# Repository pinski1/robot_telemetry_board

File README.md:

# Robot Telemetry Board

[Telemetry firmware available here](https://github.com/mjg59/robot_telemetry_viewer)

board files in ./board

schematic in ./output

See the "bridge" directory for code to use this board as an opto-isolated
USB serial bridge.

See the "analysis" directory for code used to analyze the resulting logs.

You can [buy the PCB directly from
OSHPark](https://oshpark.com/shared_projects/APZSUiwL) if you'd like to use it.

If you use the board, it would be super cool of you to give us credit.

The BOM is in BOM.csv

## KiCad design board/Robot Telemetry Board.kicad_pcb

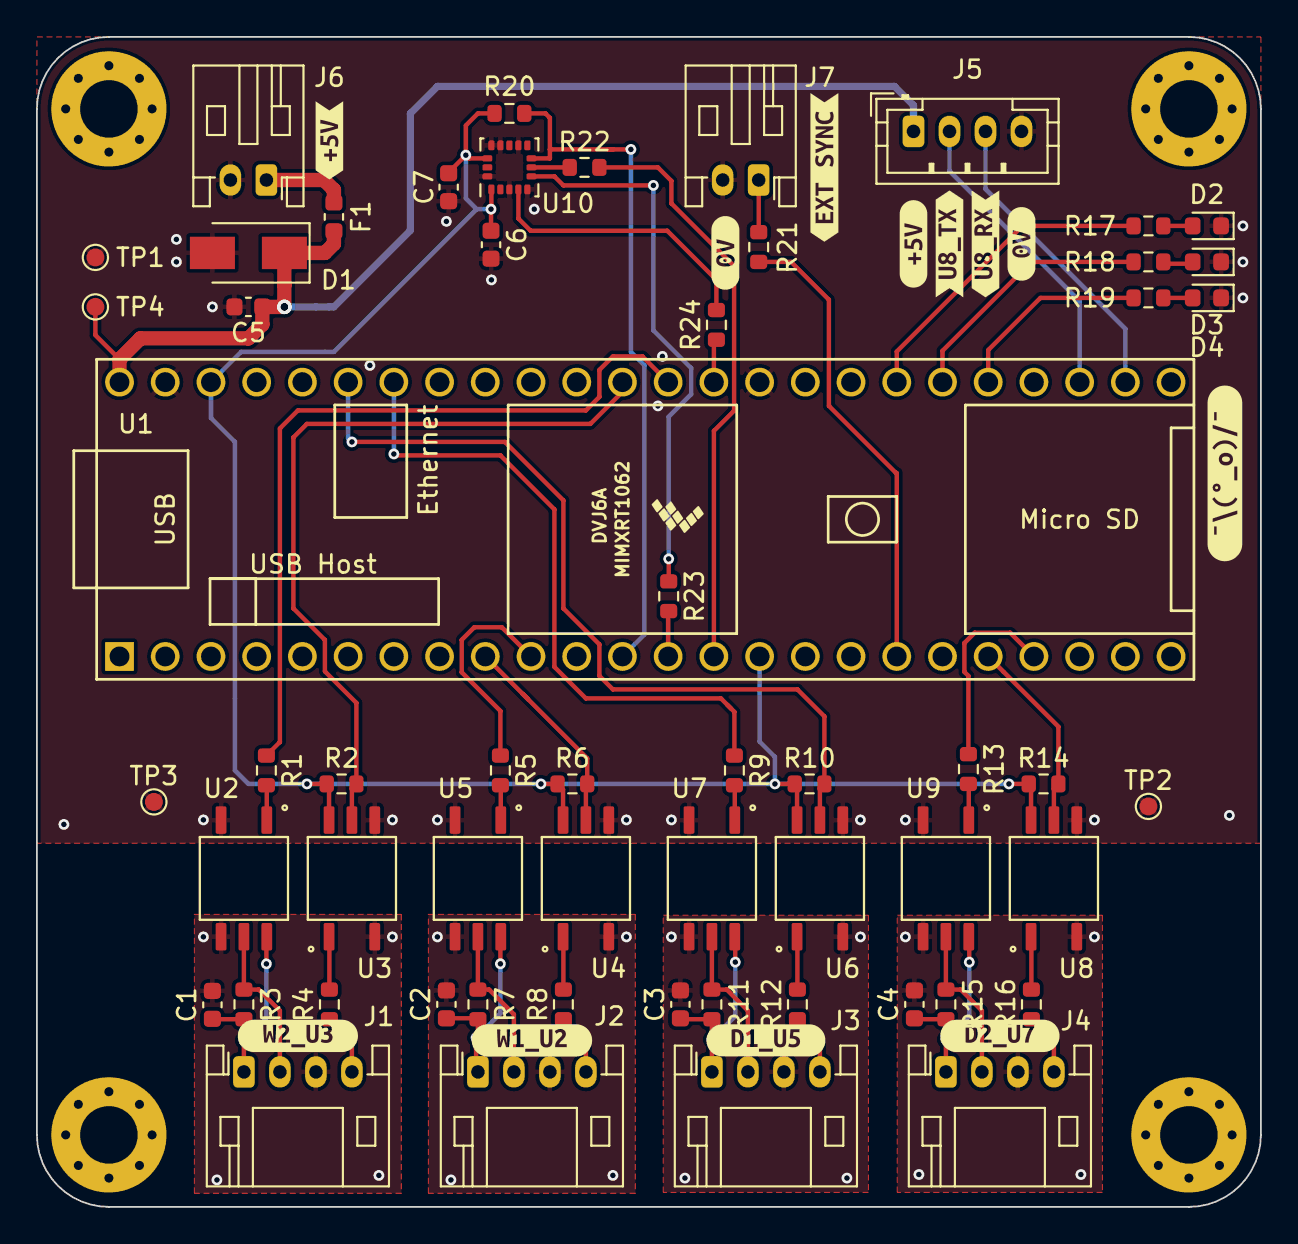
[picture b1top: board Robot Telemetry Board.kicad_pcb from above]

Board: 2 copper layers, 68.0 x 65.0 mm, 73 parts (0 on the bottom side), 53 nets.

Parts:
C1, C2, C3, C4, C6, C7: 100nF; C_0603_1608Metric
C5: 1uF; C_0603_1608Metric
D1: SMAJ5.0AQ-13-F; D_SMA
D2, D3, D4: LED; LED_0603_1608Metric
F1: 200mA; Fuse_0603_1608Metric
H1, H2, H3, H4: MountingHole; MountingHole_3.2mm_M3_Pad_Via
J1, J2, J3, J4: Conn_01x04; JST_PH_S4B-PH-K_1x04_P2.00mm_Horizontal
J5: Conn_01x04; JST_PH_B4B-PH-K_1x04_P2.00mm_Vertical
J6, J7: Conn_01x02; JST_PH_S2B-PH-K_1x02_P2.00mm_Horizontal
R1, R2, R3, R4, R5, R6, R7, R8, R9, R10, R11, R12, R13, R14, R15, R16, R17, R18, R19: 1k; R_0603_1608Metric
R20: 10k; R_0603_1608Metric
R21, R22, R23, R24: 100R; R_0603_1608Metric
TP1, TP2, TP3, TP4: TestPoint; TestPoint_Pad_D1.0mm
U1: Teensy4.1; Teensy41_DIP
U2, U3, U4, U5, U6, U7, U8, U9: VOM452T; SOIC127P700X230-5N
U10: ADXL372; LGA-16_3x3mm_P0.5mm_LayoutBorder3x5y
kibuzzard-61D772F0: G***; kibuzzard-61D772F0
kibuzzard-61D773E1: G***; kibuzzard-61D773E1
kibuzzard-61D773F7: G***; kibuzzard-61D773F7
kibuzzard-61D7731E: G***; kibuzzard-61D7731E
kibuzzard-61D7737B, kibuzzard-61D7737B#2: G***; kibuzzard-61D7737B
kibuzzard-61D7742A: G***; kibuzzard-61D7742A
kibuzzard-61D7757F: G***; kibuzzard-61D7757F
kibuzzard-61D77360: G***; kibuzzard-61D77360
kibuzzard-61D77558: G***; kibuzzard-61D77558
kibuzzard-61D77572: G***; kibuzzard-61D77572
kibuzzard-61D77595: G***; kibuzzard-61D77595

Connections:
+3V3: C6.1, C7.1, R2.1, R6.1, R10.1, R14.1, R20.2, U1.15 (3V3), U1.46 (3V3), U3.6, U4.6, U6.6, U8.6, U10.1 (VDDIO), U10.14 (VS)
+5V: C5.1, D1.1 (A1), F1.1, J5.1, TP4.1, U1.48 (VIN)
/D_VESC1_UART5_RX: R10.2, U1.43 (21_A7_RX5_BCLK1), U6.5
/D_VESC1_UART5_TX: R9.1, U1.42 (20_A6_TX5_LRCLK1)
/D_VESC2_UART7_RX: R14.2, U1.20 (28_RX7), U8.5
/D_VESC2_UART7_TX: R13.1, U1.21 (29_TX7)
/EXT_SYNC: R21.2, U1.18 (26_A12_MOSI1)
/ISO_UART1/ISO_RX: J1.4, R4.1
/ISO_UART1/ISO_TX: J1.2, R3.2, U2.5
/ISO_UART1/VDD: C1.1, J1.1, R3.1, U2.6
/ISO_UART1/VSS: C1.2, J1.3, U2.4, U3.3
/ISO_UART2/ISO_RX: J2.4, R8.1
/ISO_UART2/ISO_TX: J2.2, R7.2, U5.5
/ISO_UART2/VDD: C2.1, J2.1, R7.1, U5.6
/ISO_UART2/VSS: C2.2, J2.3, U4.3, U5.4
/ISO_UART3/ISO_RX: J3.4, R12.1
/ISO_UART3/ISO_TX: J3.2, R11.2, U7.5
/ISO_UART3/VDD: C3.1, J3.1, R11.1, U7.6
/ISO_UART3/VSS: C3.2, J3.3, U6.3, U7.4
/ISO_UART4/ISO_RX: J4.4, R16.1
/ISO_UART4/ISO_TX: J4.2, R15.2, U9.5
/ISO_UART4/VDD: C4.1, J4.1, R15.1, U9.6
/ISO_UART4/VSS: C4.2, J4.3, U8.3, U9.4
/LED1: R17.1, U1.31 (39_MISO1_OUT1A)
/LED2: R18.1, U1.30 (38_CS1_IN1)
/LED3: R19.1, U1.29 (37_CS)
/SPI_MISO: R22.2, U1.14 (12_MISO_MQSL)
/SPI_MOSI: R23.1, U10.6 (MOSI/SDA)
/SPI_SCK: R24.2, U10.4 (SCLK)
/SPI_~CS: R20.1, U1.12 (10_CS_MQSR), U10.8 (~CS/SCL)
/UART8_RX: J5.3, U1.26 (34_RX8)
/UART8_TX: J5.2, U1.27 (35_TX8)
/W_VESC1_UART2_RX: R6.2, U1.9 (7_RX2_OUT1A), U4.5
/W_VESC1_UART2_TX: R5.1, U1.10 (8_TX2_IN1)
/W_VESC2_UART3_RX: R2.2, U1.37 (15_A1_RX3_SPDIF_IN), U3.5
/W_VESC2_UART3_TX: R1.1, U1.36 (14_A0_TX3_SPDIF_OUT)
GND: C5.2, C6.2, C7.2, D1.2 (A2), D2.1 (K), D3.1 (K), D4.1 (K), J5.4, J6.2, J7.2, TP1.1, TP2.1, TP3.1, U1.34 (GND), U1.47 (GND), U2.3, U3.4, U4.4, U5.3, U6.4, U7.3, U8.4, U9.3, U10.3 (RESERVED), U10.5 (RESERVED), U10.10 (RESERVED), U10.12 (GND), U10.13 (GND), U10.16 (GND)
unnamed: D2.2 (A), R17.2
unnamed: D3.2 (A), R18.2
unnamed: D4.2 (A), R19.2
unnamed: F1.2, J6.1
unnamed: J7.1, R21.1
unnamed: R5.2, U5.1
unnamed: R8.2, U4.1
unnamed: R9.2, U7.1
unnamed: R12.2, U6.1
unnamed: R13.2, U9.1
unnamed: R16.2, U8.1
unnamed: R22.1, U10.7 (MISO)
unnamed: R23.2, U1.13 (11_MOSI_CTX1)
unnamed: R24.1, U1.35 (13_SCK_LED)
unnamed: R1.2, U2.1
unnamed: R4.2, U3.1

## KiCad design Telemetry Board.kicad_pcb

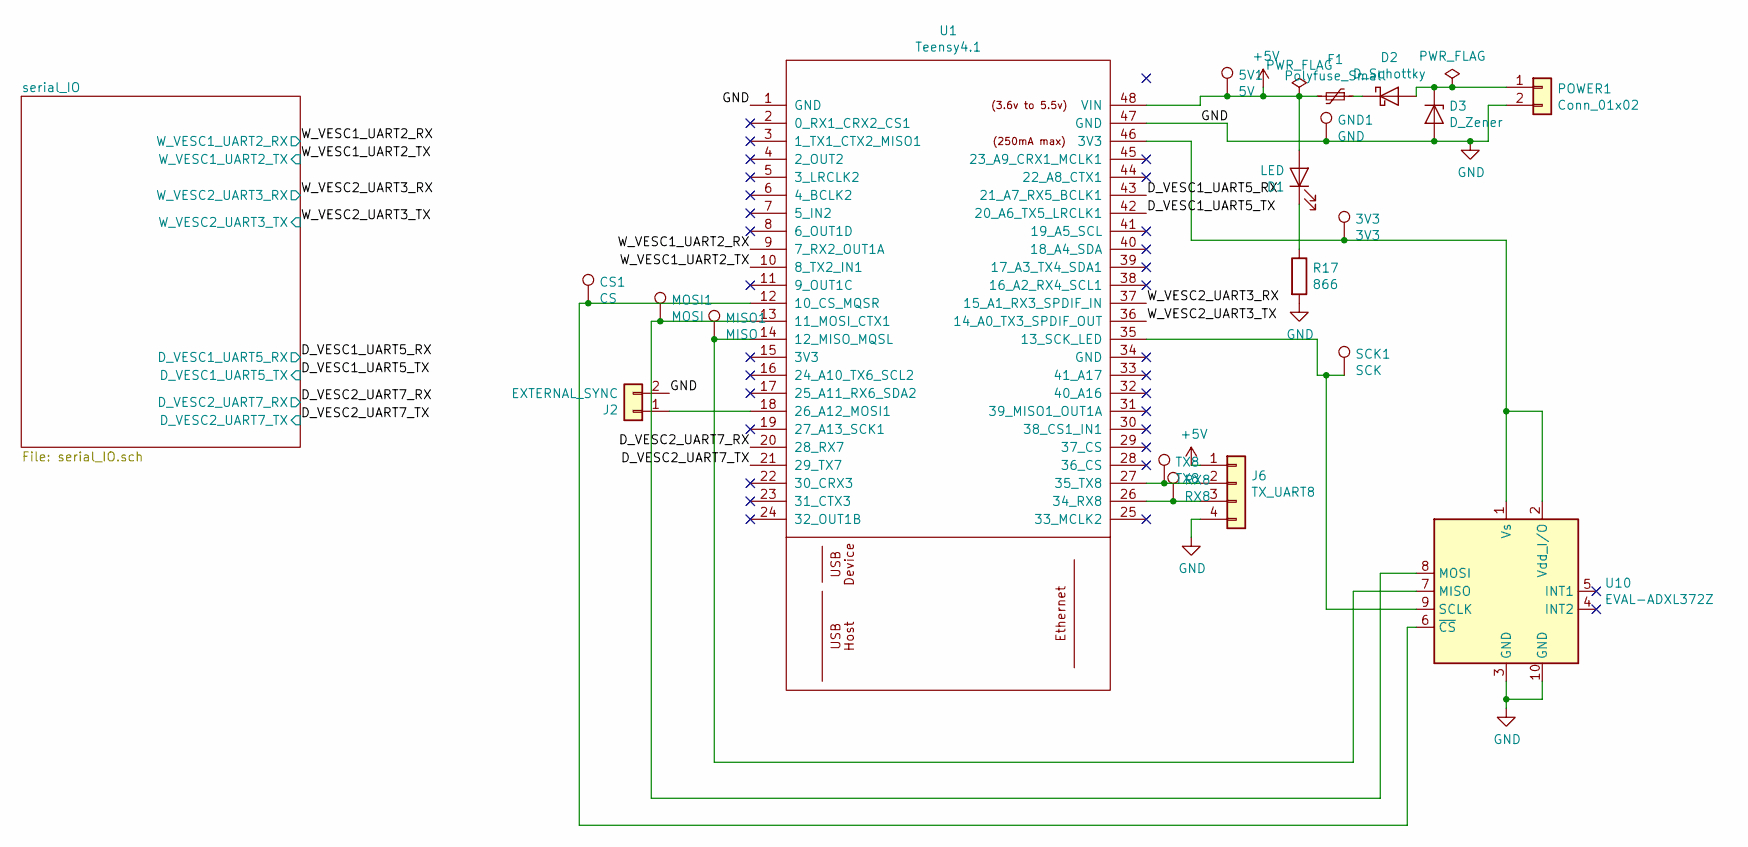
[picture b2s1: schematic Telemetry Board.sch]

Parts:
3V3: 3V3; TestPoint_Pad_D1.5mm
5V1: 5V; TestPoint_Pad_D1.5mm
CS1: CS; TestPoint_Pad_D1.5mm
D1: LED; LED_0603_1608Metric_Pad1.05x0.95mm_HandSolder
D2: D_Schottky; D_0603_1608Metric_Pad1.05x0.95mm_HandSolder
D3: D_Zener; D_SMA_Handsoldering
F1: Polyfuse_Small; Fuse_0603_1608Metric_Pad1.05x0.95mm_HandSolder
GND1: GND; TestPoint_Pad_D1.5mm
J2: EXTERNAL_SYNC; JST_PH_B2B-PH-K_1x02_P2.00mm_Vertical
J6: TX_UART8; JST_PH_B4B-PH-K_1x04_P2.00mm_Vertical
MISO1: MISO; TestPoint_Pad_D1.5mm
MOSI1: MOSI; TestPoint_Pad_D1.5mm
POWER1: Conn_01x02; JST_PH_B2B-PH-K_1x02_P2.00mm_Vertical
R17: 866; R_0603_1608Metric_Pad1.05x0.95mm_HandSolder
RX8: RX8; TestPoint_Pad_D1.5mm
SCK1: SCK; TestPoint_Pad_D1.5mm
TX8: TX8; TestPoint_Pad_D1.5mm
U1: Teensy4.1; Teensy41
U10: EVAL-ADXL372Z; EVAL-ADXL372X

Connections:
+5V: 5V1.1, D1.2 (A), F1.2, J6.1, U1.48 (VIN); also elsewhere on the board
/D_VESC1_UART5_RX: U1.43 (21_A7_RX5_BCLK1); also elsewhere on the board
/D_VESC1_UART5_TX: U1.42 (20_A6_TX5_LRCLK1); also elsewhere on the board
/D_VESC2_UART7_RX: U1.20 (28_RX7); also elsewhere on the board
/D_VESC2_UART7_TX: U1.21 (29_TX7); also elsewhere on the board
/W_VESC1_UART2_RX: U1.9 (7_RX2_OUT1A); also elsewhere on the board
/W_VESC1_UART2_TX: U1.10 (8_TX2_IN1); also elsewhere on the board
/W_VESC2_UART3_RX: U1.37 (15_A1_RX3_SPDIF_IN); also elsewhere on the board
/W_VESC2_UART3_TX: U1.36 (14_A0_TX3_SPDIF_OUT); also elsewhere on the board
GND: D3.2 (A), GND1.1, J2.2, J6.4, POWER1.2, R17.2, U1.1 (GND), U1.47 (GND), U10.3 (GND), U10.10 (GND); also elsewhere on the board
unnamed: 3V3.1, U1.46 (3V3), U10.1 (Vs), U10.2 (Vdd_I/O)
unnamed: CS1.1, U1.12 (10_CS_MQSR), U10.6 (~CS)
unnamed: D1.1 (K), R17.1
unnamed: D2.1 (K), F1.1
unnamed: D2.2 (A), D3.1 (K), POWER1.1
unnamed: J2.1, U1.18 (26_A12_MOSI1)
unnamed: J6.2, TX8.1, U1.27 (35_TX8)
unnamed: J6.3, RX8.1, U1.26 (34_RX8)
unnamed: MISO1.1, U1.14 (12_MISO_MQSL), U10.7 (MISO)
unnamed: MOSI1.1, U1.13 (11_MOSI_CTX1), U10.8 (MOSI)
unnamed: SCK1.1, U1.35 (13_SCK_LED), U10.9 (SCLK)

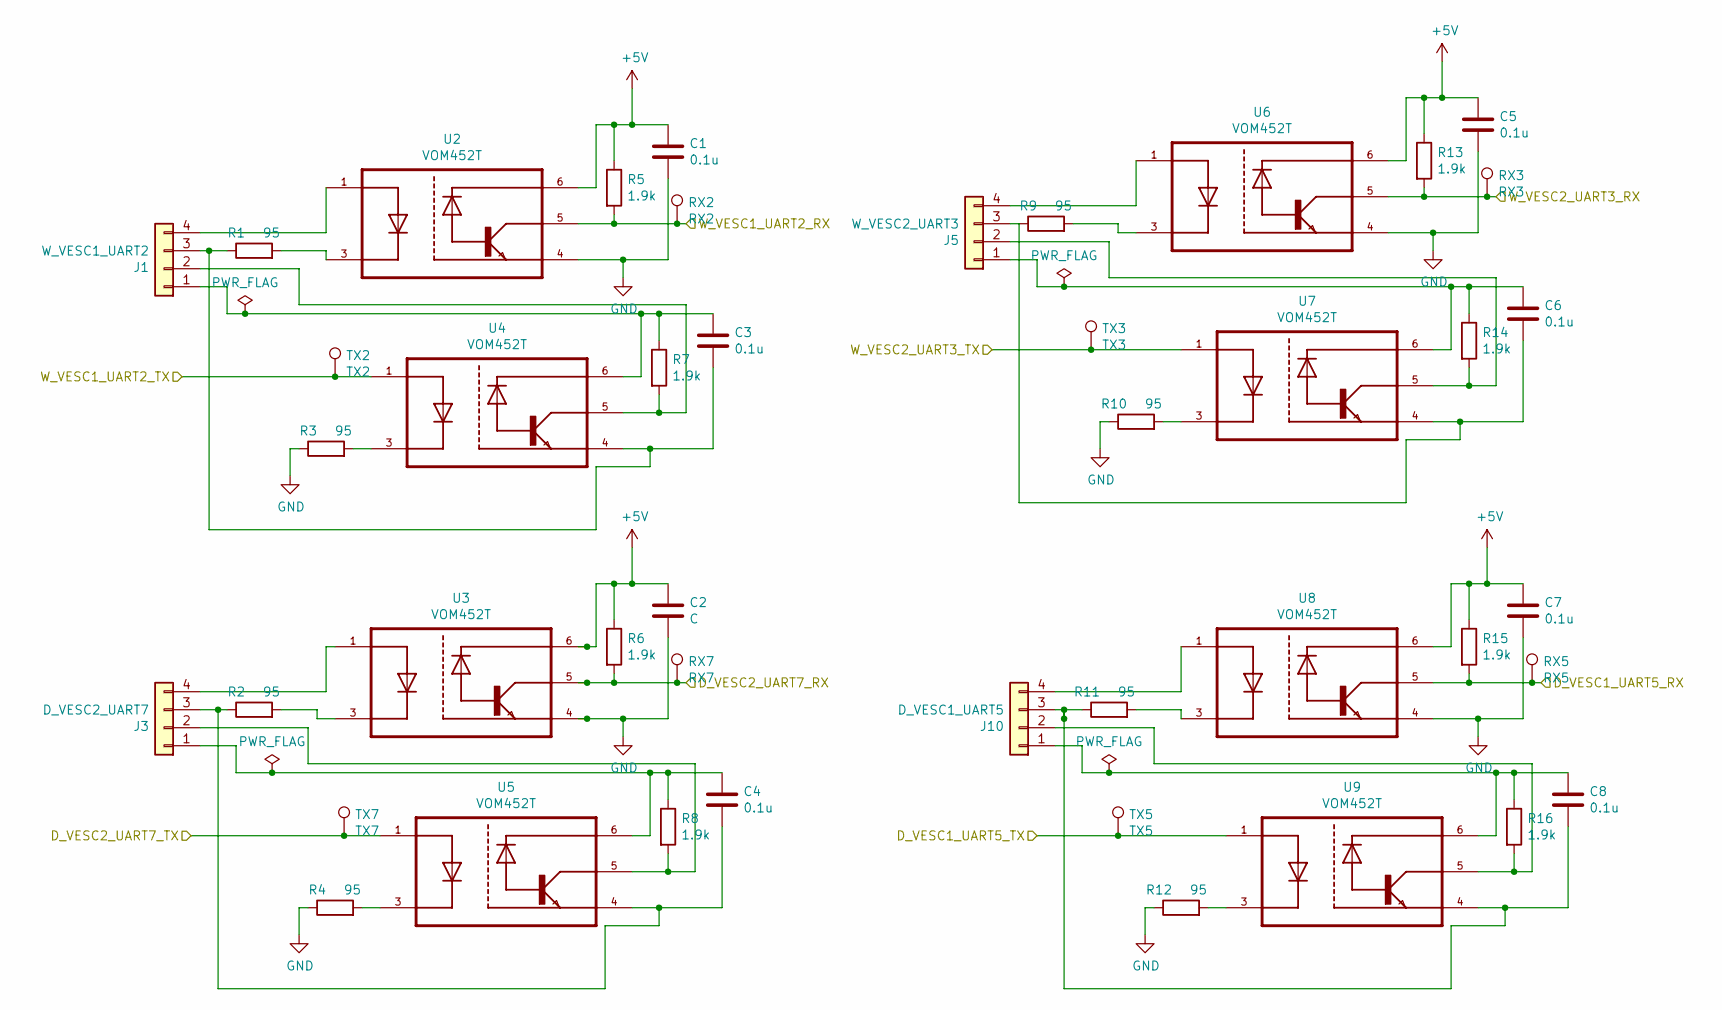
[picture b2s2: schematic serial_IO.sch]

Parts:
C1, C3, C4, C5, C6, C7, C8: 0.1u; C_0603_1608Metric_Pad1.05x0.95mm_HandSolder
C2: C; C_0603_1608Metric_Pad1.05x0.95mm_HandSolder
J1: W_VESC1_UART2; JST_PH_B4B-PH-K_1x04_P2.00mm_Vertical
J3: D_VESC2_UART7; JST_PH_B4B-PH-K_1x04_P2.00mm_Vertical
J5: W_VESC2_UART3; JST_PH_B4B-PH-K_1x04_P2.00mm_Vertical
J10: D_VESC1_UART5; JST_PH_B4B-PH-K_1x04_P2.00mm_Vertical
R1, R2, R3, R4, R9, R10, R11, R12: 95; R_0603_1608Metric_Pad1.05x0.95mm_HandSolder
R5, R6, R7, R8, R13, R14, R15, R16: 1.9k; R_0603_1608Metric_Pad1.05x0.95mm_HandSolder
RX2: RX2; TestPoint_Pad_D1.5mm
RX3: RX3; TestPoint_Pad_D1.5mm
RX5: RX5; TestPoint_Pad_D1.5mm
RX7: RX7; TestPoint_Pad_D1.5mm
TX2: TX2; TestPoint_Pad_D1.5mm
TX3: TX3; TestPoint_Pad_D1.5mm
TX5: TX5; TestPoint_Pad_D1.5mm
TX7: TX7; TestPoint_Pad_D1.5mm
U2, U3, U4, U5, U6, U7, U8, U9: VOM452T; SOIC127P700X230-5N

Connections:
+5V: C1.1, C2.1, C5.1, C7.1, R5.1, R6.1, R13.1, R15.1, U2.6, U3.6, U6.6, U8.6; also elsewhere on the board
/D_VESC1_UART5_RX: R15.2, RX5.1, U8.5; also elsewhere on the board
/D_VESC1_UART5_TX: TX5.1, U9.1; also elsewhere on the board
/D_VESC2_UART7_RX: R6.2, RX7.1, U3.5; also elsewhere on the board
/D_VESC2_UART7_TX: TX7.1, U5.1; also elsewhere on the board
/W_VESC1_UART2_RX: R5.2, RX2.1, U2.5; also elsewhere on the board
/W_VESC1_UART2_TX: TX2.1, U4.1; also elsewhere on the board
/W_VESC2_UART3_RX: R13.2, RX3.1, U6.5; also elsewhere on the board
/W_VESC2_UART3_TX: TX3.1, U7.1; also elsewhere on the board
GND: C1.2, C2.2, C5.2, C7.2, R3.1, R4.1, R10.1, R12.1, U2.4, U3.4, U6.4, U8.4; also elsewhere on the board
unnamed: C3.1, J1.1, R7.1, U4.6
unnamed: C3.2, J1.3, R1.1, U4.4
unnamed: C4.1, J3.1, R8.1, U5.6
unnamed: C4.2, J3.3, R2.1, U5.4
unnamed: C6.1, J5.1, R14.1, U7.6
unnamed: C6.2, J5.3, R9.1, U7.4
unnamed: C8.1, J10.1, R16.1, U9.6
unnamed: C8.2, J10.3, R11.1, U9.4
unnamed: J1.2, R7.2, U4.5
unnamed: J1.4, U2.1
unnamed: J3.2, R8.2, U5.5
unnamed: J3.4, U3.1
unnamed: J5.2, R14.2, U7.5
unnamed: J5.4, U6.1
unnamed: J10.2, R16.2, U9.5
unnamed: J10.4, U8.1
unnamed: R1.2, U2.3
unnamed: R2.2, U3.3
unnamed: R3.2, U4.3
unnamed: R4.2, U5.3
unnamed: R9.2, U6.3
unnamed: R10.2, U7.3
unnamed: R11.2, U8.3
unnamed: R12.2, U9.3

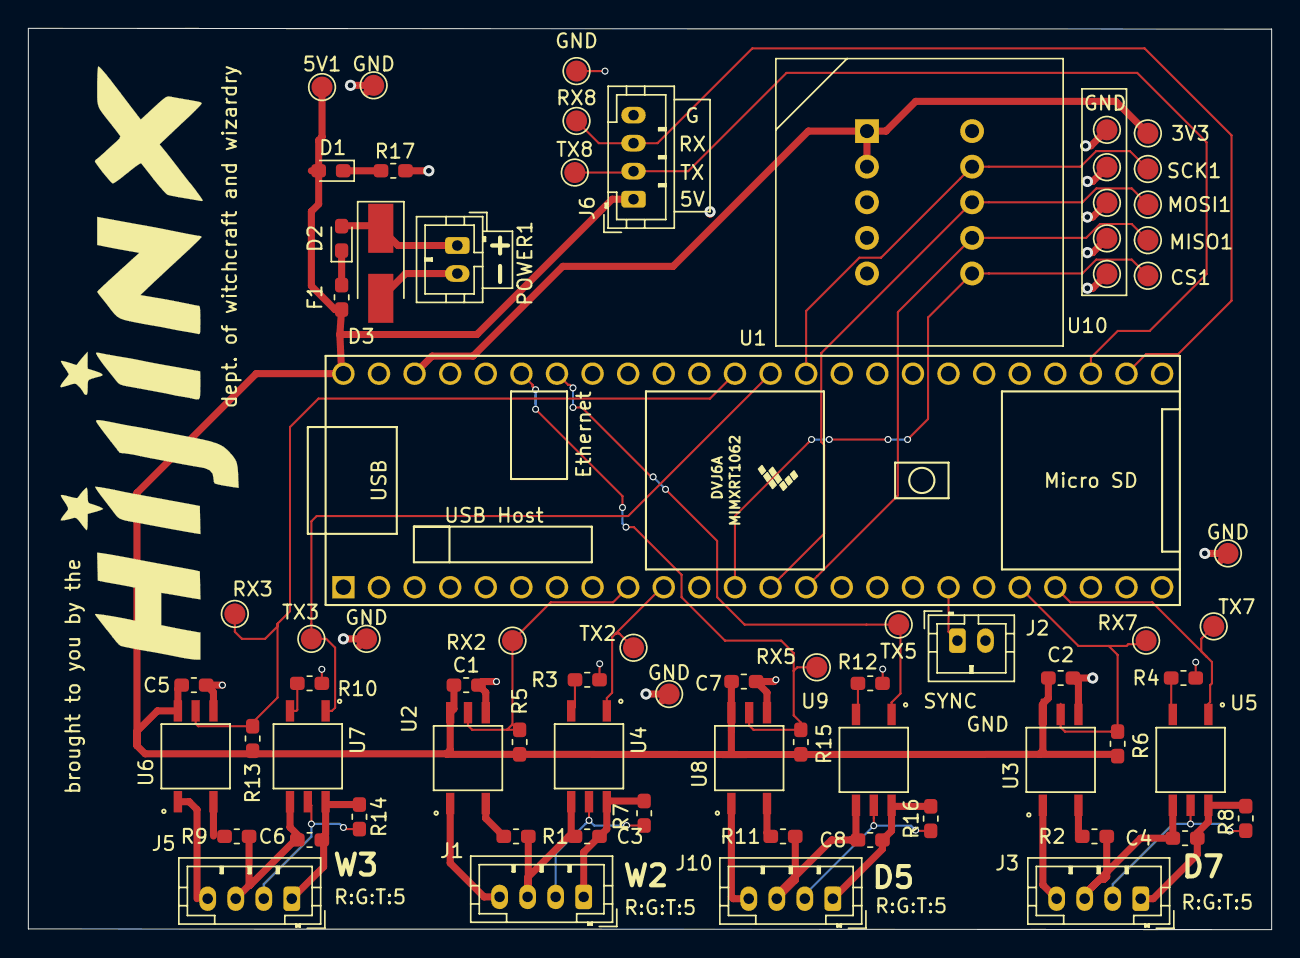
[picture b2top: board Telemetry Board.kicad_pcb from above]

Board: 2 copper layers, 88.7 x 64.3 mm, 72 parts (0 on the bottom side), 45 nets.

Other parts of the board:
GND1#2, GND1#3, GND1#4, GND1#5, GND1#6, GND1#7, GND1#8, GND1#9, GND1#10: GND; TestPoint_Pad_D1.5mm

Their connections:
GND: GND1#2.1, GND1#3.1, GND1#4.1, GND1#5.1, GND1#6.1, GND1#7.1, GND1#8.1, GND1#9.1, GND1#10.1; also elsewhere on the board

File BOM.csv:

Part,,,Part number,Board location,Number of parts per board,number of parts for 7 boards,datasheet,ordered
optocouplers,Vishay VOM452T 1MBps optocoupler,,https://www.mouser.com/ProductDetail/Vishay-Semiconductors/V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,"U6, U7, U2, U4, U8, U9, U3, U5",8,56,,x
radio,,,,,1,7,,
accelerometer,EVAL-ADXL372Z,,,U1,1,7,,
input resistor,95 ohms,"""0603""",https://www.mouser.com/ProductDetail/YAGEO/RC0603JR-7W100RL?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,"R9, R10, R1, R3, R11, R12, R2, R4",8,56,,x
output resistor,1.9k,"""0603""",https://www.mouser.com/ProductDetail/755-SDR03EZPJ182,"R13, R14, R5, R7, R15, R16, R6, R8",8,56,,x
power led resistor,840 ohms,"""0603""",https://www.mouser.com/ProductDetail/Panasonic/ERJ-PA3F8660V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,R17,1,7,,x
output cap,0.1 uF,"""0603""",https://www.mouser.com/ProductDetail/Taiyo-Yuden/LMK107B7224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,"C5, C6, C1, C3, C7, C8, C2, C4",8,56,,x
2-pin conector,Connector_JST:JST_PH_B2B-PH-K_1x02_P2.00mm_Vertical,,,"POWER1, J2",2,14,,
4-pin connector,Connector_JST:JST_PH_B4B-PH-K_1x04_P2.00mm_Vertical,,,"J5, J1, J10, J3, J6",5,35,,
power LED,,"""0603""",https://www.mouser.com/ProductDetail/859-LTST-C194TBKT,D1,1,7,,
5V TVS,,,https://www.mouser.com/ProductDetail/Diodes-Incorporated/SMA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,D3,1,7,,
reverse voltage protection diode,,"""0603""",https://www.mouser.com/ProductDetail/Comchip-Technology/CDBU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,D2,1,7,,
0603 ptc,,,https://www.mouser.com/ProductDetail/Littelfuse/0603L020YR?q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,F1,1,7,https://www.mouser.com/datasheet/2/240/Littelfuse_PTC_0603L_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,
"0.1"" pin strip",5,,https://www.mouser.com/ProductDetail/Preci-dip/350-10-105-00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,For EVAL-ADXL372Z,2,14,,
"0.1"" pin strip",24,,https://www.mouser.com/ProductDetail/Molex/90120-0784?qs=PvP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,For Teensy 4.1,2,14,,
Teensy 4.1,,,,,,,,

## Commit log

2021-09-09 Add design files
2021-09-15 Add analysis script
2021-09-15 Correct link destination, add analysis to main README
2022-01-03 applying the shrinkray!
2022-01-03 updating the readme.md
2022-01-03 Completing the top half
2022-01-03 updating optocouplers
2022-01-03 Updating pdf
2022-01-05 Adding LCSC part numbers
2022-01-06 Adding some labels
2022-01-06 need a gitignore!
